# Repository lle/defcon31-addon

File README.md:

# DEFCON31 BLINKY BADGE-ADDON
This project recycles the same schematic and foundation code from my Snake Business Card. The main difference is that there is only a single button on the PCB that the user can interact with. In the development of this project, STM32 CubeMX and CubeIDE were used to configure and generate the HAL (hardware-abstraction-layer). Some says I'm cheating and using a code generator. I don't disagree XD.

To edit/compile/flash the code you only need to install CubeIDE. Although feel free to use any tools you like. 
You can download CubeIDE here: https://www.st.com/en/development-tools/stm32cubeide.html

## Code and Game Behavior
The badge-addon is loaded with a set of animation. The animation is selected in the main loop in "main.c". There is a switch statement that cycles between each animation. When the button is pressed, the animation is incremented to select a new one. Each animation is described in a specific .c/.h file
* anim_name.c 
* anim_random.c
* anim_swipe.c

You can add additional animation by adding a new .c/.h pair. Add an #include in main.c and call the your animation function in the switch statement.

## About the Timer16
The clock is set to 8Mhz and the timer16 counter is set to 1000 (see "tim.c"). Thus 8Mhz/1000=8Khz.
The timer runs at 8khz. It updates a new LED 8000 cycles per second. 

### Analogy
Imagine there is a cursor that is moving left to right, top to bottom. Every cycle, the cursor moves to the next LED, reads the buffer and decides if the LED should be on/off. In other words, it takes 64 cycles to update the full screen since there is 64 LEDs. Consequently, it takes 8000Hz/64LEDs = 125ms to update the full screen.

### Where is the timer handler?
The timer handler function "HAL_TIM_PeriodElapsedCallback()" is called in the file "stm32f0xx_it.c". At that location the "screen_interruptUpdate()" function is called to update the next LED.

## About LED Matrix
The chip we are using is the STM32F0. The datasheet indicates that the maximum current through a whole GPIO PORT is 30mA. The LEDs are running at 20mA with the chosen current limit resistor. Therefore, the code is set to only turn on 1 single LED at a time in order to satisfy that requirement. Since the whole screen is updated every 125ms, there is enough persistence of vision to produce a consistent animation.

The low-level function which controls the individual LEDs is located in "ledHandler.c". The function 
"matrix_setLed_on()" is used to enable an LED. It can be seen that at the beginning of it, it calls "matrix_setLed_allOff()" to disable any previous LEDs and ensure the PORT never source more than 30mA.

## About screenBuffer.c
The screenBuffer is how you interact with the LED matrix. There is 1 main fundamental fonction you need:
* screen_set_bit(row, column, state)

This is function set the state of each LEDs in the 8x8 matrix. It's either 1 (on) or 0 (off).

Additionally, there are helper functions to make animating easier:
* screen_get_bit()
* screen_fill()	
* screen_clear()

## How to Flash
Things you need:
* ST-Link - I personally use an STM32F0 Nucleo Board: [497-15096-ND](https://www.digikey.ca/en/products/detail/stmicroelectronics/NUCLEO-F072RB/5047984)
* Female Connector: [H2193-ND](https://www.digikey.ca/en/products/detail/hirose-electric-co-ltd/DF13-4P-1-25DSA/241767?s=N4IgTCBcDaIBJgIwE4DMBaAcgERAXQF8g)
* Male Connector: [H2181-ND](https://www.digikey.ca/en/products/detail/hirose-electric-co-ltd/DF13-4S-1-25C/241750)
* Precrimped wires x4: [H4BXG-10112-B8-ND](https://www.digikey.ca/en/products/detail/hirose-electric-co-ltd/H4BXG-10112-B8/426117)

### Instruction
* Connect the ST-Link SWD header to the PCB's programming port

* Compile the code in STM CubeIDE: "Project"->"Build All"
* Connect your Nucleo board to your computer
* Configure the debugger as follows: "Run" -> "Debug Configurations"

* Flash the firmware: "Run" -> "Run"
* You will see this in the logs
```
Memory Programming ...
Opening and parsing file: ST-LINK_GDB_server_a15460.srec
  File          : ST-LINK_GDB_server_a15460.srec
  Size          : 21.34 KB 
  Address       : 0x08000000 
Erasing memory corresponding to segment 0:
Erasing internal memory sectors [0 21]
Download in Progress:
File download complete
Time elapsed during download operation: 00:00:01.454
Verifying ...
Download verified successfully 
Shutting down...
Exit.
```
* You might have to power cycle the PCB to get the firmware started the first time
* Congrats, you have flashed the addon. Happy coding.

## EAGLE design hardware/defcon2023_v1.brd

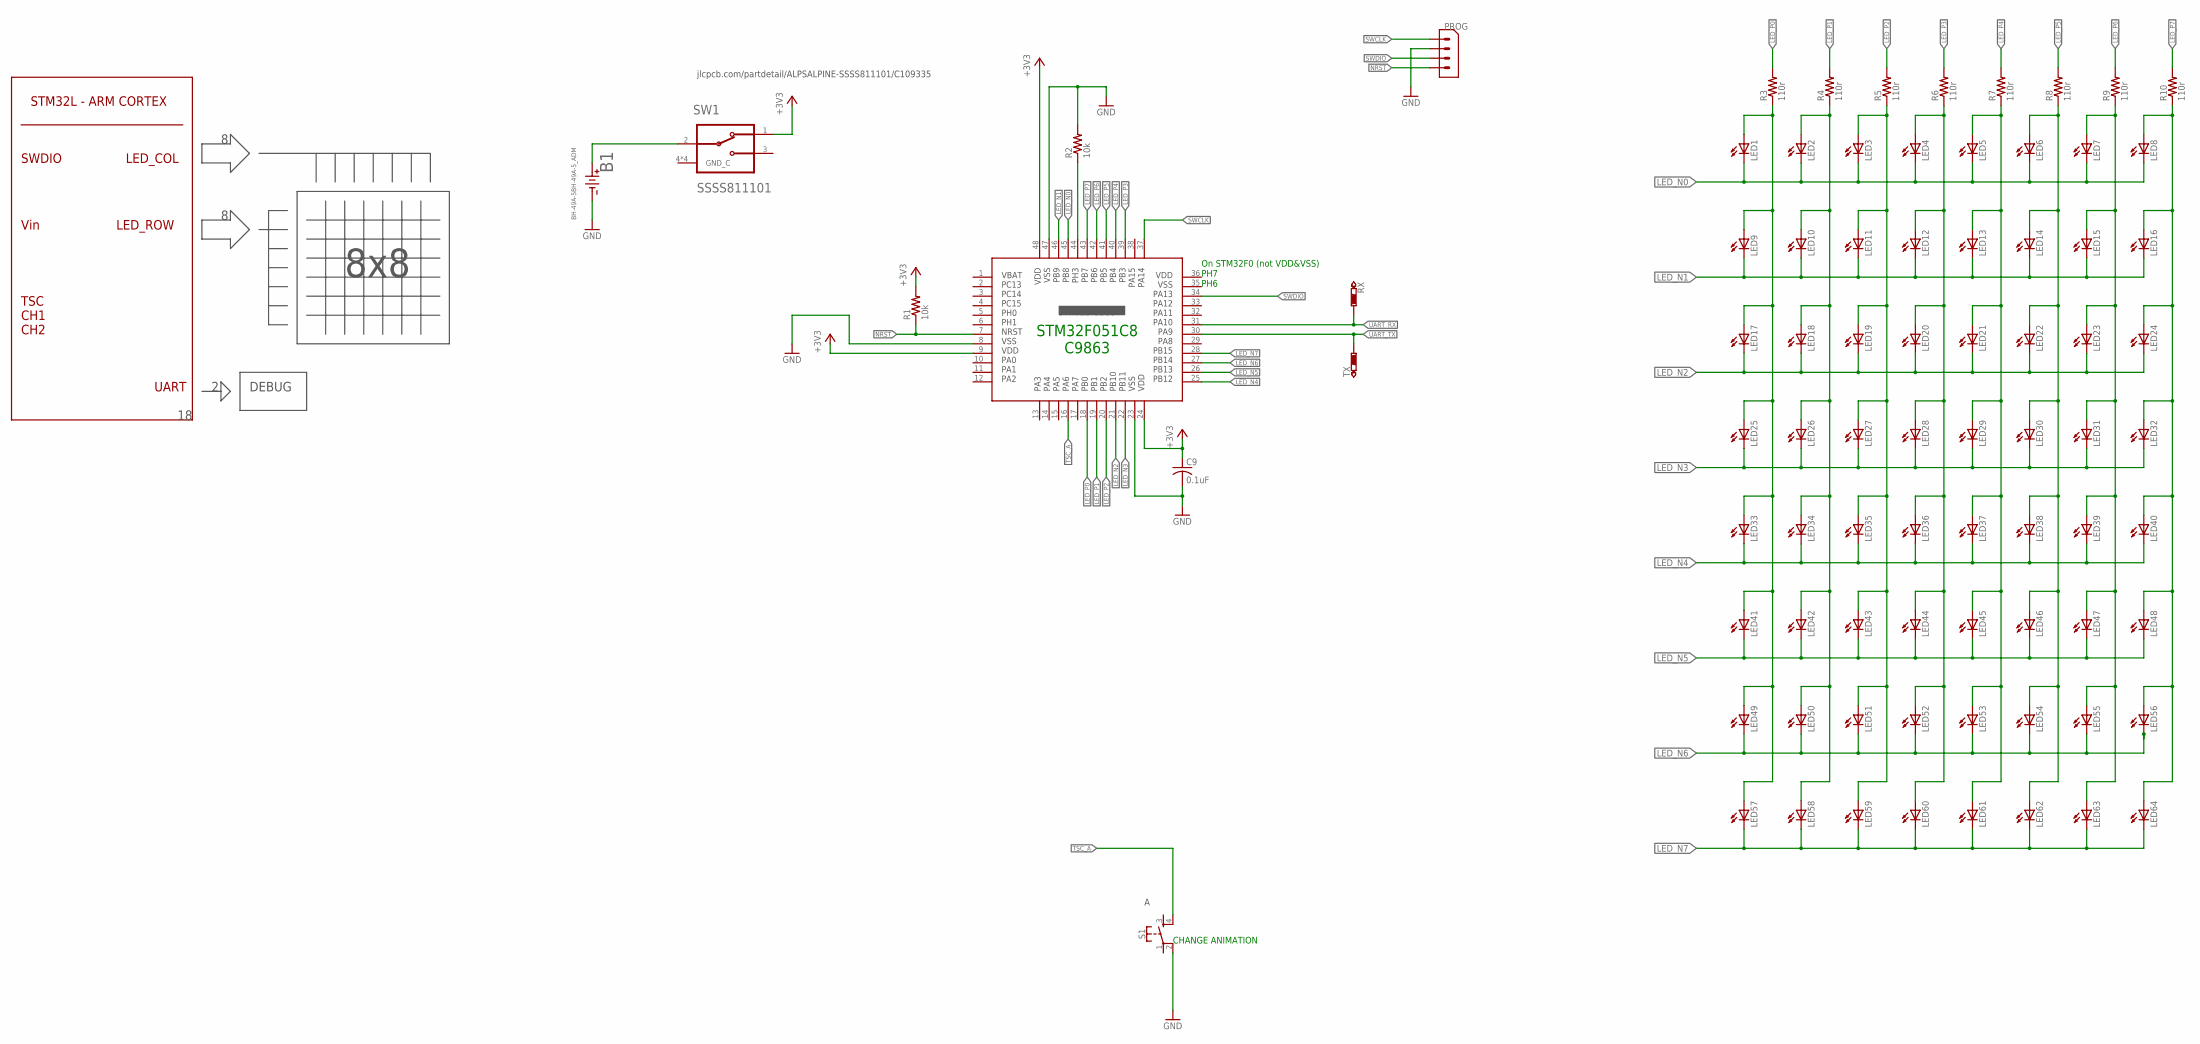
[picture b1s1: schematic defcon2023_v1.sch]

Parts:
B1: BH-49A-5BH-49A-5_ADM; BH-49A-5_ADM
C9: 0.1uF; C0603
LED1, LED2, LED3, LED4, LED5, LED6, LED7, LED8, LED9, LED10, LED11, LED12, LED13, LED14, LED15, LED16, LED17, LED18, LED19, LED20, LED21, LED22, LED23, LED24, LED25, LED26, LED27, LED28, LED29, LED30, LED31, LED32, LED33, LED34, LED35, LED36, LED37, LED38, LED39, LED40, LED41, LED42, LED43, LED44, LED45, LED46, LED47, LED48, LED49, LED50, LED51, LED52, LED53, LED54, LED55, LED56, LED57, LED58, LED59, LED60, LED61, LED62, LED63, LED64: LEDCHIP-LED0603; CHIP-LED0603
PROG: 4-PIN-1.25MM
R1, R2: 10k; R0603
R3, R4, R5, R6, R7, R8, R9, R10: 110r; R0603
RX: PTR1B1,27; B1,27
S1: MOMENTARY-SWITCH-SPST-2-SMD-5.2MM; TACTILE_SWITCH_SMD_5.2MM
SW1: ALPS_SSSS811101ALPS_SSSS811101_0_0; ALPS_SSSS811101_0
TX: PTR1B1,27; B1,27
U$2: STM32L431CC; QFP50P900X900X160-48

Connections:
+3V3: C9.1, R1.2, SW1.1, U$2.9, U$2.24, U$2.48
GND: B1.2, C9.2, PROG.P$3 (2), R2.2, S1.2, U$2.8, U$2.23, U$2.47
LED_N0: LED1.C, LED2.C, LED3.C, LED4.C, LED5.C, LED6.C, LED7.C, LED8.C, U$2.45
LED_N1: LED9.C, LED10.C, LED11.C, LED12.C, LED13.C, LED14.C, LED15.C, LED16.C, U$2.46
LED_N2: LED17.C, LED18.C, LED19.C, LED20.C, LED21.C, LED22.C, LED23.C, LED24.C, U$2.21
LED_N3: LED25.C, LED26.C, LED27.C, LED28.C, LED29.C, LED30.C, LED31.C, LED32.C, U$2.22
LED_N4: LED33.C, LED34.C, LED35.C, LED36.C, LED37.C, LED38.C, LED39.C, LED40.C, U$2.25
LED_N5: LED41.C, LED42.C, LED43.C, LED44.C, LED45.C, LED46.C, LED47.C, LED48.C, U$2.26
LED_N6: LED49.C, LED50.C, LED51.C, LED52.C, LED53.C, LED54.C, LED55.C, LED56.C, U$2.27
LED_N7: LED57.C, LED58.C, LED59.C, LED60.C, LED61.C, LED62.C, LED63.C, LED64.C, U$2.28
LED_P0: R3.2, U$2.18
LED_P0B: LED1.A, LED9.A, LED17.A, LED25.A, LED33.A, LED41.A, LED49.A, LED57.A, R3.1
LED_P1: R4.2, U$2.19
LED_P1B: LED2.A, LED10.A, LED18.A, LED26.A, LED34.A, LED42.A, LED50.A, LED58.A, R4.1
LED_P2: R5.2, U$2.20
LED_P2B: LED3.A, LED11.A, LED19.A, LED27.A, LED35.A, LED43.A, LED51.A, LED59.A, R5.1
LED_P3: R6.2, U$2.39
LED_P3B: LED4.A, LED12.A, LED20.A, LED28.A, LED36.A, LED44.A, LED52.A, LED60.A, R6.1
LED_P4: R7.2, U$2.40
LED_P4B: LED5.A, LED13.A, LED21.A, LED29.A, LED37.A, LED45.A, LED53.A, LED61.A, R7.1
LED_P5: R8.2, U$2.41
LED_P5B: LED6.A, LED14.A, LED22.A, LED30.A, LED38.A, LED46.A, LED54.A, LED62.A, R8.1
LED_P6: R9.2, U$2.42
LED_P6B: LED7.A, LED15.A, LED23.A, LED31.A, LED39.A, LED47.A, LED55.A, LED63.A, R9.1
LED_P7: R10.2, U$2.43
LED_P7B: LED8.A, LED16.A, LED24.A, LED32.A, LED40.A, LED48.A, LED56.A, LED64.A, R10.1
unnamed: R2.1, U$2.44
unnamed: B1.1, SW1.2 (C)
NRST: PROG.P$1 (4), R1.1, U$2.7
SWCLK: PROG.P$4 (1), U$2.37
SWDIO: PROG.P$2 (3), U$2.34
TSC_A: S1.4, U$2.16
UART_RX: RX.TP, U$2.31
UART_TX: TX.TP, U$2.30

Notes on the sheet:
SWDIO
Vin
LED_COL
LED_ROW
TSC CH1 CH2
STM32L - ARM CORTEX
DEBUG
UART
8x8
jlcpcb.com/partdetail/ALPSALPINE-SSSS811101/C109335
STM32F051C8 C9863
On STM32F0 (not VDD&VSS) PH7 PH6
CHANGE ANIMATION

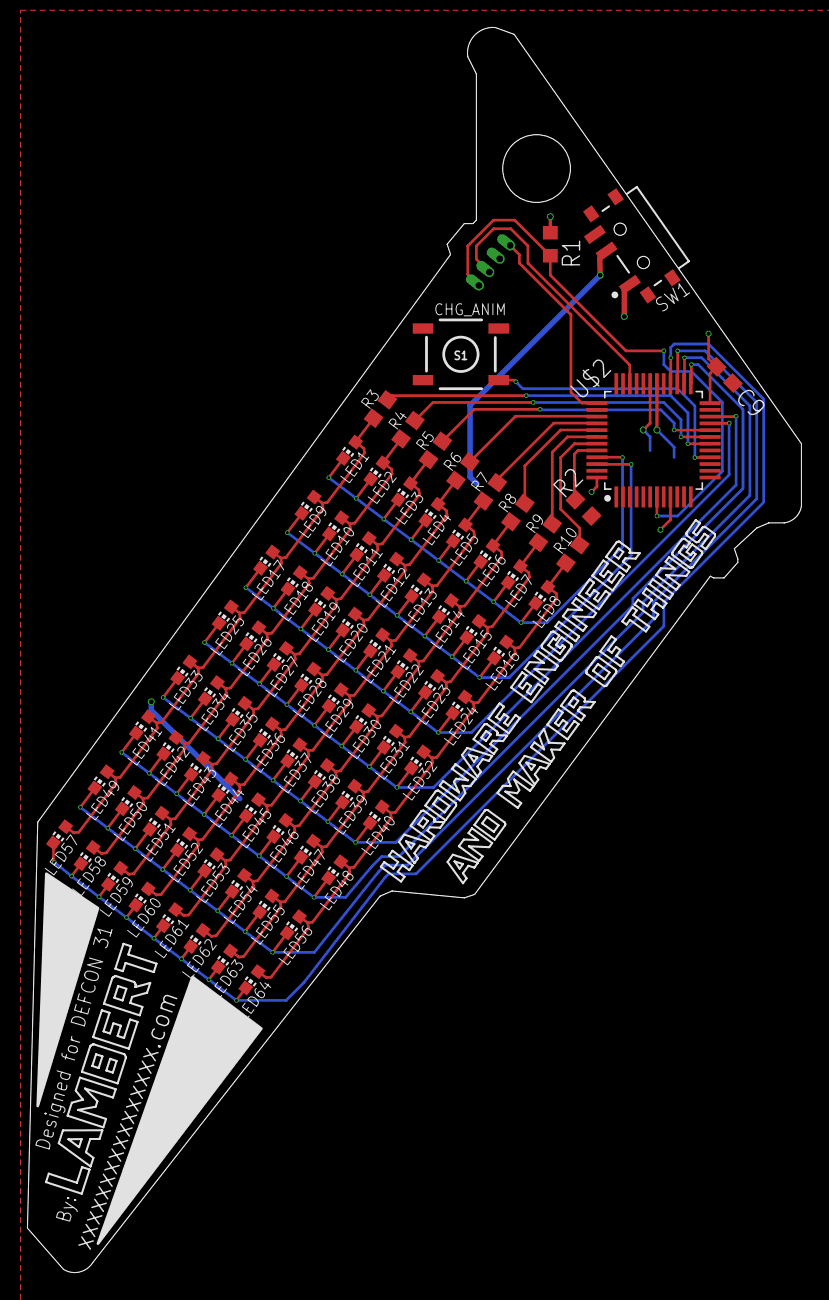
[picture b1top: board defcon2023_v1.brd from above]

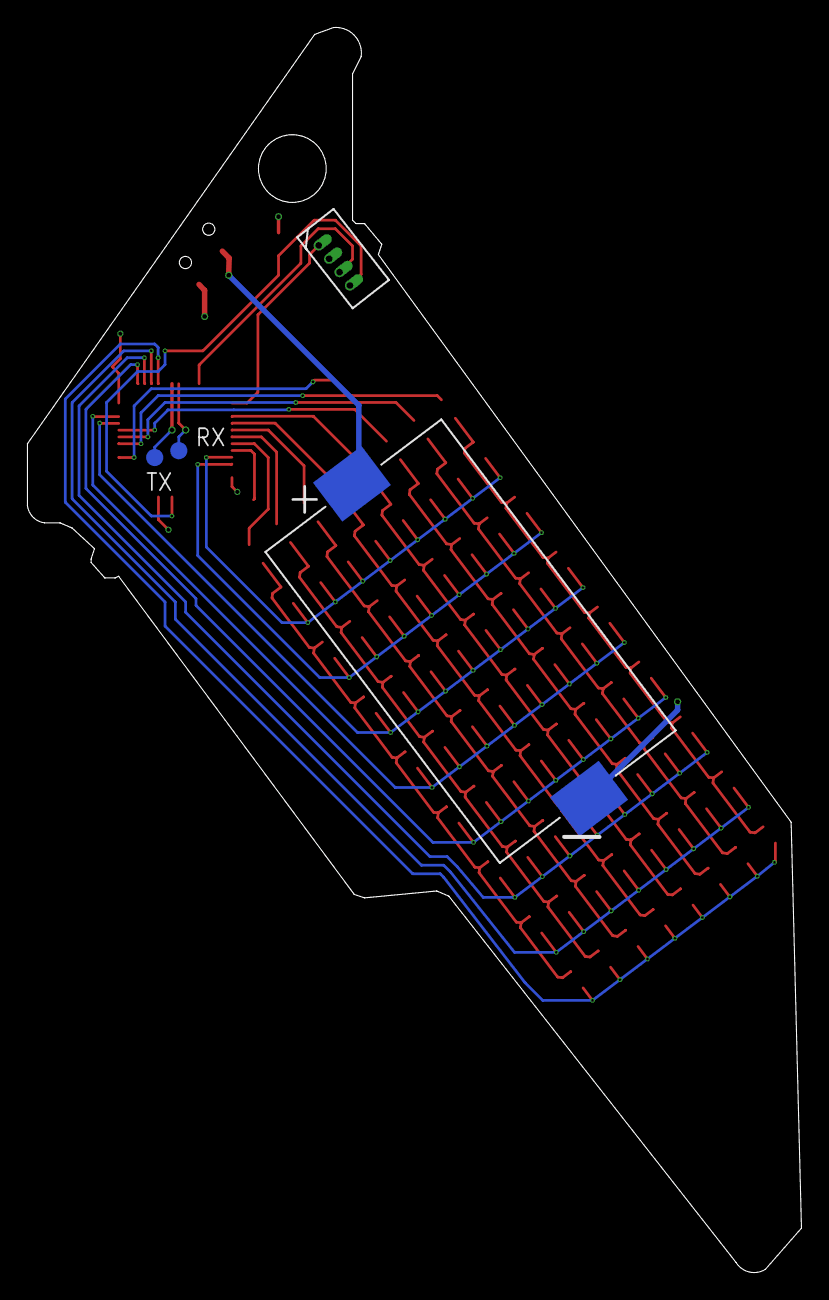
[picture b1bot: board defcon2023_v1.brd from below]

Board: 2 copper layers, 57.1 x 91.9 mm, 82 parts (4 on the bottom side), 34 nets.

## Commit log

2023-07-20 Initial clone code of snakeBusinessCard
2023-07-23 added first wave of animation
2023-07-23 correct delay() syntax
2023-08-06 Add hardware files
2023-08-06 Updated "name" animation timing
2023-08-06 added schematic+pcb PNG
2023-08-08 Add git ignore
2023-08-08 More efficient anim_name
2023-08-08 Added DrawLine function
2023-08-08 Added Rotation demo and converted swipes to draw_line
2023-08-08 add basic animation reader
2023-08-08 Moved screen draw functions to screenBuffer
2023-08-08 Added conway's game of life from github.com/mtagius/game-of-life-8x8-arduino-matrix
2023-08-08 Added conway's game of life to menu and permitted menu to hold more than 9 animations.
2023-08-19 Added Readme
2023-08-19 added missing maunal
2023-08-19 restructured folders
2023-08-19 Updated to latest STM32 HAL
2023-08-20 Added more info in readme
2023-09-09 Added instructions to flash
2023-09-09 Added conclusion

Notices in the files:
parts and their libraries:
SparkFun-Switches: Licensing: Creative Commons ShareAlike 4.0 International - https://creativecommons.org/licenses/by-sa/4.0
2057-BH-49A-5-ND: COPYRIGHT: Copyright (C) 2023 Ultra Librarian. All rights reserved.
